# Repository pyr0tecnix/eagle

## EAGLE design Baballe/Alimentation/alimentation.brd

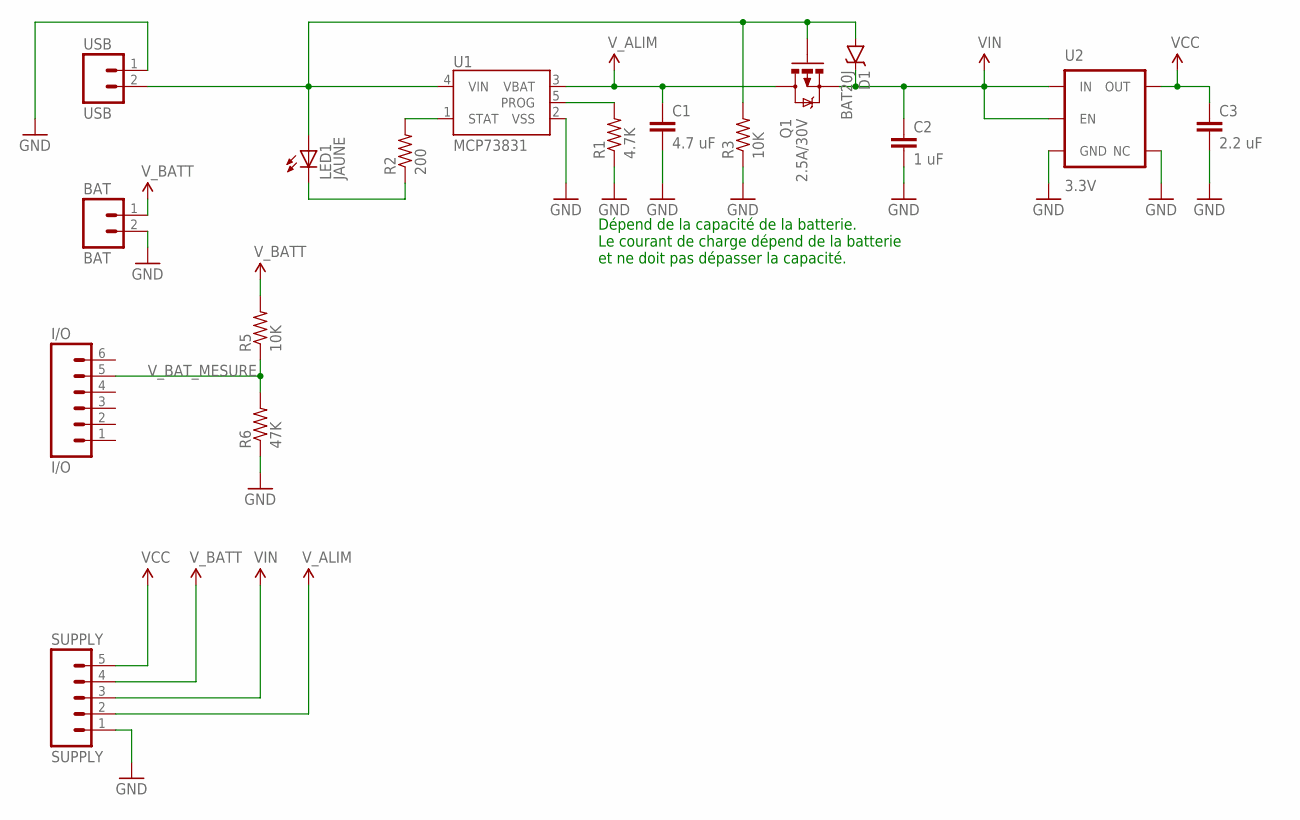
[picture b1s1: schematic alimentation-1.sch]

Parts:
BAT: BAT; 1X02_NO_SILK
C1: 4.7 uF; 0805
C2: 1 uF; 0805
C3: 2.2 uF; 0805
D1: BAT20J; SOD-323
I/O: I/O; 1X06_NO_SILK
LED1: JAUNE; LED_1206
Q1: 2.5A/30V; SOT23-3
R1: 4.7K; 0805
R2: 200; 0805
R3, R5: 10K; 0805
R6: 47K; 0805
SUPPLY: SUPPLY; 1X05_NO_SILK
U1: MCP73831; SOT23-5
U2: 3.3V; SOT23-5
USB: USB; 1X02_NO_SILK

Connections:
GND: BAT.2, C1.2, C2.2, C3.2, R1.1, R3.1, R6.1, SUPPLY.1, U1.2 (VSS), U2.2 (GND), U2.4 (NC), USB.1
unnamed: LED1.C, R2.1
unnamed: R1.2, U1.5 (PROG)
unnamed: R2.2, U1.1 (STAT)
VCC: C3.1, SUPPLY.5, U2.5 (OUT)
VCC_2: C1.1, Q1.3 (D), SUPPLY.2, U1.3 (VBAT)
VIN: C2.1, D1.C, Q1.2 (S), SUPPLY.3, U2.1 (IN), U2.3 (EN)
VUSB: D1.A, LED1.A, Q1.1 (G), R3.2, U1.4 (VIN), USB.2
V_BATT: BAT.1, R5.2, SUPPLY.4
V_BAT_MESURE: I/O.5, R5.1, R6.2

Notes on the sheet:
Dépend de la capacité de la batterie. Le courant de charge dépend de la batterie et ne doit pas dépasser la capacité.

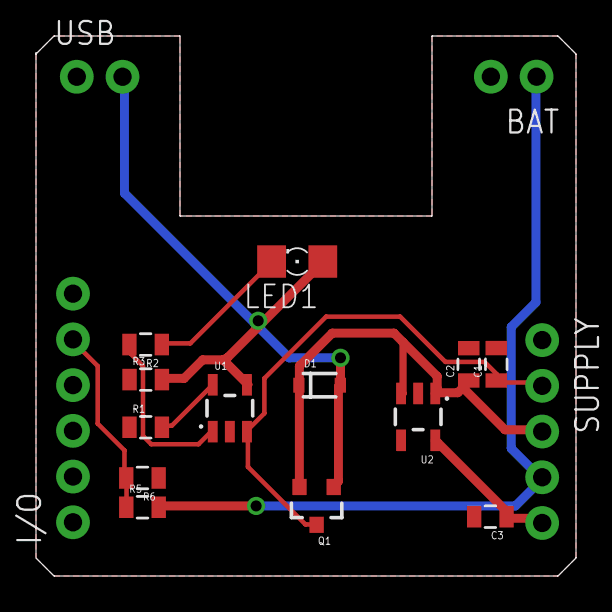
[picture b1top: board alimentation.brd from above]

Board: 2 copper layers, 30.0 x 30.0 mm, 17 parts (0 on the bottom side), 10 nets.

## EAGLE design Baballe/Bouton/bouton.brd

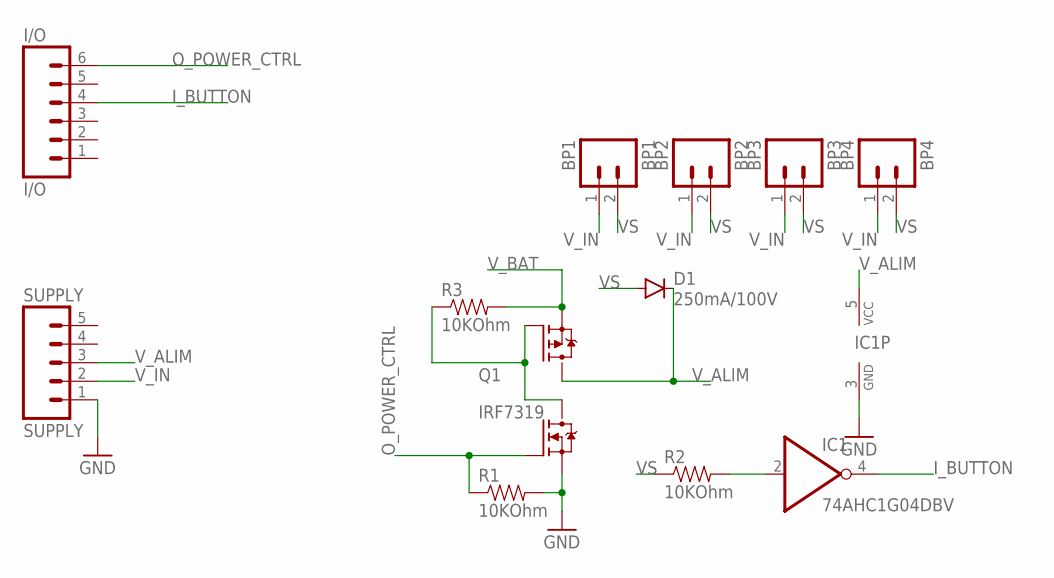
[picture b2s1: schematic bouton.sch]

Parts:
BP1: BP1; 1X02_NO_SILK
BP2: BP2; 1X02_NO_SILK
BP3: BP3; 1X02_NO_SILK
BP4: BP4; 1X02_NO_SILK
D1: 250mA/100V; SOD-323
I/O: I/O; 1X06_NO_SILK
IC1: 74AHC1G04DBV; SOT23-5
Q1: IRF7319; SO08-IRF
R1, R2, R3: 10KOhm; 0805
SUPPLY: SUPPLY; 1X05_NO_SILK

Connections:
GND: IC1.3 (GND), Q1.1 (N-S), R1.2, SUPPLY.1
I_BUTTON: I/O.4, IC1.4 (O)
unnamed: Q1.4 (P-G), Q1.7 (N-D), Q1.8 (N-D), R3.1
unnamed: IC1.2 (I), R2.2
O_POWER_CTRL: I/O.6, Q1.2 (N-G), R1.1
VS: BP1.2, BP2.2, BP3.2, BP4.2, D1.A, R2.1
V_ALIM: D1.C, IC1.5 (VCC), Q1.5 (P-D), Q1.6 (P-D), SUPPLY.3
V_BAT: Q1.3 (P-S), R3.2
V_IN: BP1.1, BP2.1, BP3.1, BP4.1, SUPPLY.2

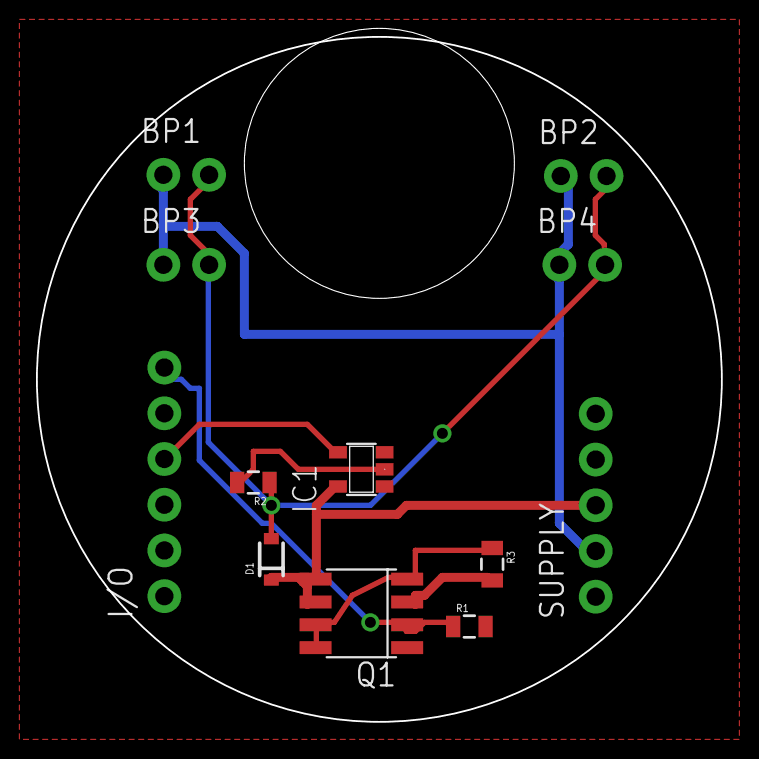
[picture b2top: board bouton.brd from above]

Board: 2 copper layers, 38.1 x 38.1 mm, 12 parts (0 on the bottom side), 9 nets.

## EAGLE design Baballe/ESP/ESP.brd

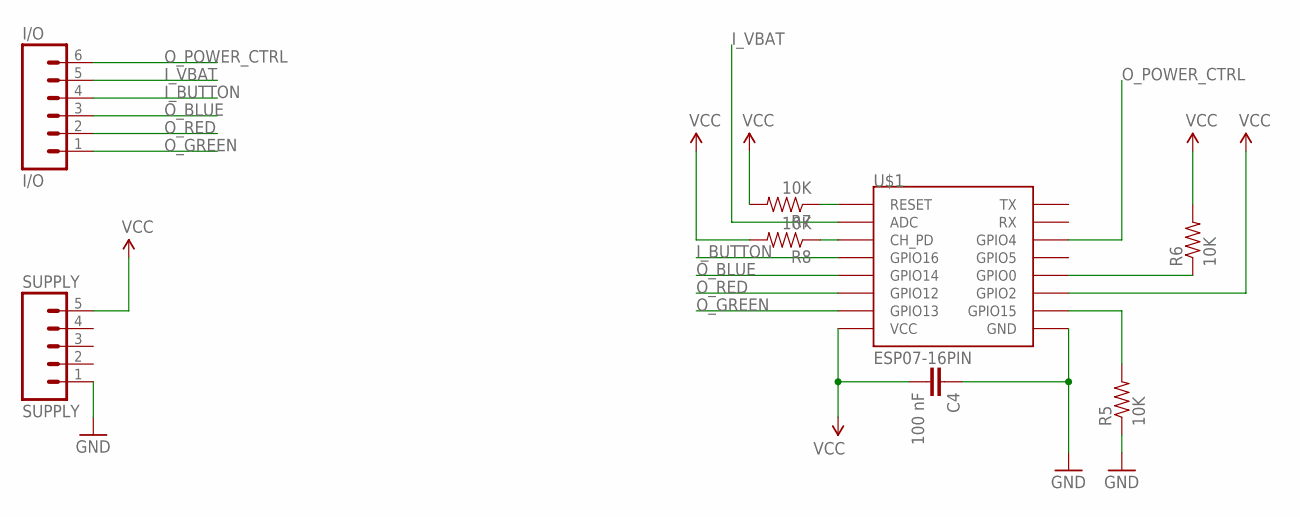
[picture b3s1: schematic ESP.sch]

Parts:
C4: 100 nF; 0805
I/O: I/O; 1X06_NO_SILK
R5, R6, R7, R8: 10K; 0805
SUPPLY: SUPPLY; 1X05_NO_SILK
U$1: ESP07-16PIN

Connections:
GND: C4.1, R5.1, SUPPLY.1, U$1.GND
I_BUTTON: I/O.4, U$1.GPIO16
I_VBAT: I/O.5, U$1.ADC
unnamed: R5.2, U$1.GPIO15
unnamed: R6.1, U$1.GPIO0
unnamed: R7.1, U$1.REST (RESET)
unnamed: R8.1, U$1.CH_PD
O_BLUE: I/O.3, U$1.GPIO14
O_GREEN: I/O.1, U$1.GPIO13
O_POWER_CTRL: I/O.6, U$1.GPIO4
O_RED: I/O.2, U$1.GPIO12
VCC: C4.2, R6.2, R7.2, R8.2, SUPPLY.5, U$1.GPIO2, U$1.VCC

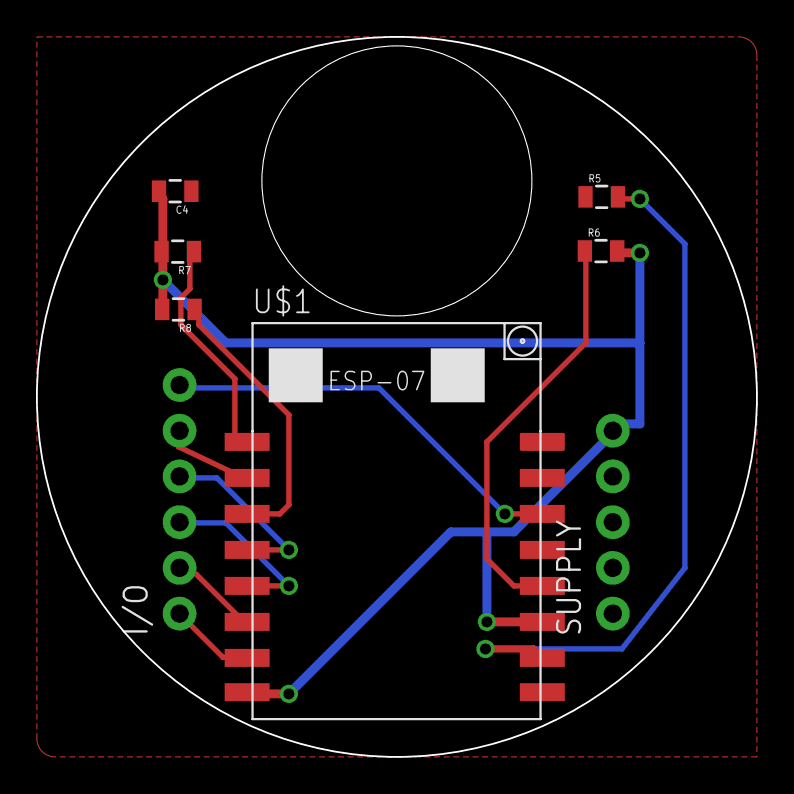
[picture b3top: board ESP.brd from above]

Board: 2 copper layers, 40.0 x 40.0 mm, 8 parts (0 on the bottom side), 12 nets.

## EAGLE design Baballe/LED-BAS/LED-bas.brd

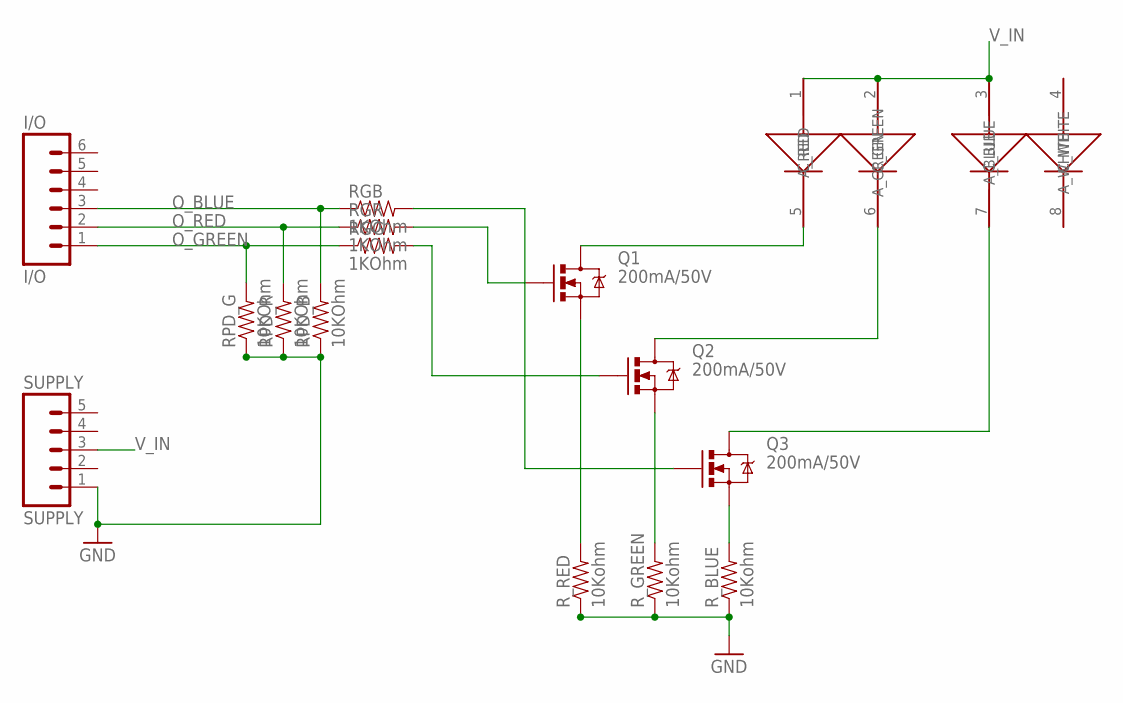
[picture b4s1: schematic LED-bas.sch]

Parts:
I/O: I/O; 1X06_NO_SILK
Q1, Q2, Q3: 200mA/50V; SOT23-3
RGB: 1KOhm; 0805
RGG: 1KOhm; 0805
RGR: 1KOhm; 0805
RPD_B: 10KOhm; 0805
RPD_G: 10KOhm; 0805
RPD_R: 10KOhm; 0805
R_BLUE: 10Kohm; 0805
R_GREEN: 10Kohm; 0805
R_RED: 10Kohm; 0805
SUPPLY: SUPPLY; 1X05_NO_SILK
U$1: CREE_MCE4CTRGBW; CLN6A

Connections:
GND: RPD_B.1, RPD_G.1, RPD_R.1, R_BLUE.1, R_GREEN.1, R_RED.1, SUPPLY.1
unnamed: Q3.2 (S), R_BLUE.2
unnamed: Q2.2 (S), R_GREEN.2
unnamed: Q1.2 (S), R_RED.2
unnamed: Q2.1 (G), RGG.2
unnamed: Q1.1 (G), RGR.2
unnamed: Q3.1 (G), RGB.2
unnamed: Q1.3 (D), U$1.5 (C_RED)
unnamed: Q2.3 (D), U$1.6 (C_GREEN)
unnamed: Q3.3 (D), U$1.7 (C_BLUE)
O_BLUE: I/O.3, RGB.1, RPD_B.2
O_GREEN: I/O.1, RGG.1, RPD_G.2
O_RED: I/O.2, RGR.1, RPD_R.2
V_IN: SUPPLY.3, U$1.1 (A_RED), U$1.2 (A_GREEN), U$1.3 (A_BLUE)

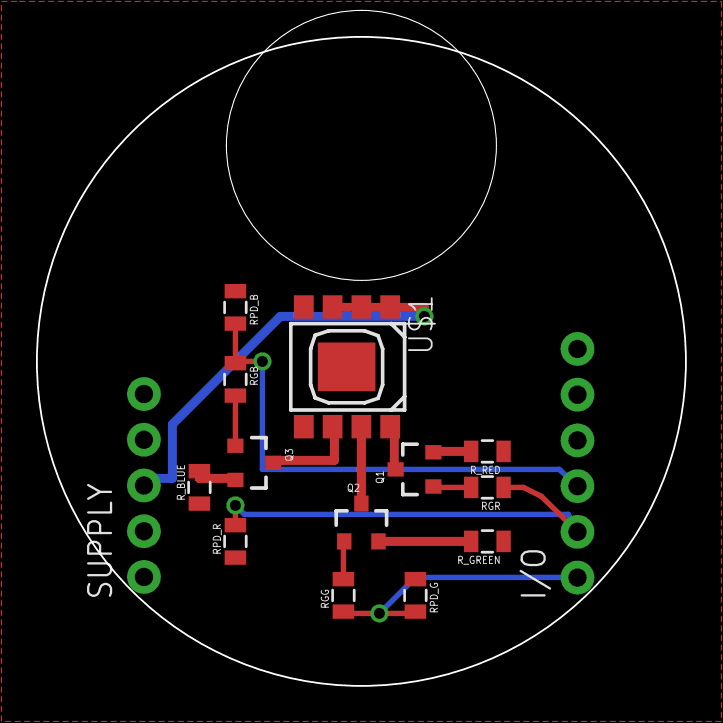
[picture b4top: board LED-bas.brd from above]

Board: 2 copper layers, 36.1 x 36.1 mm, 15 parts (0 on the bottom side), 14 nets.

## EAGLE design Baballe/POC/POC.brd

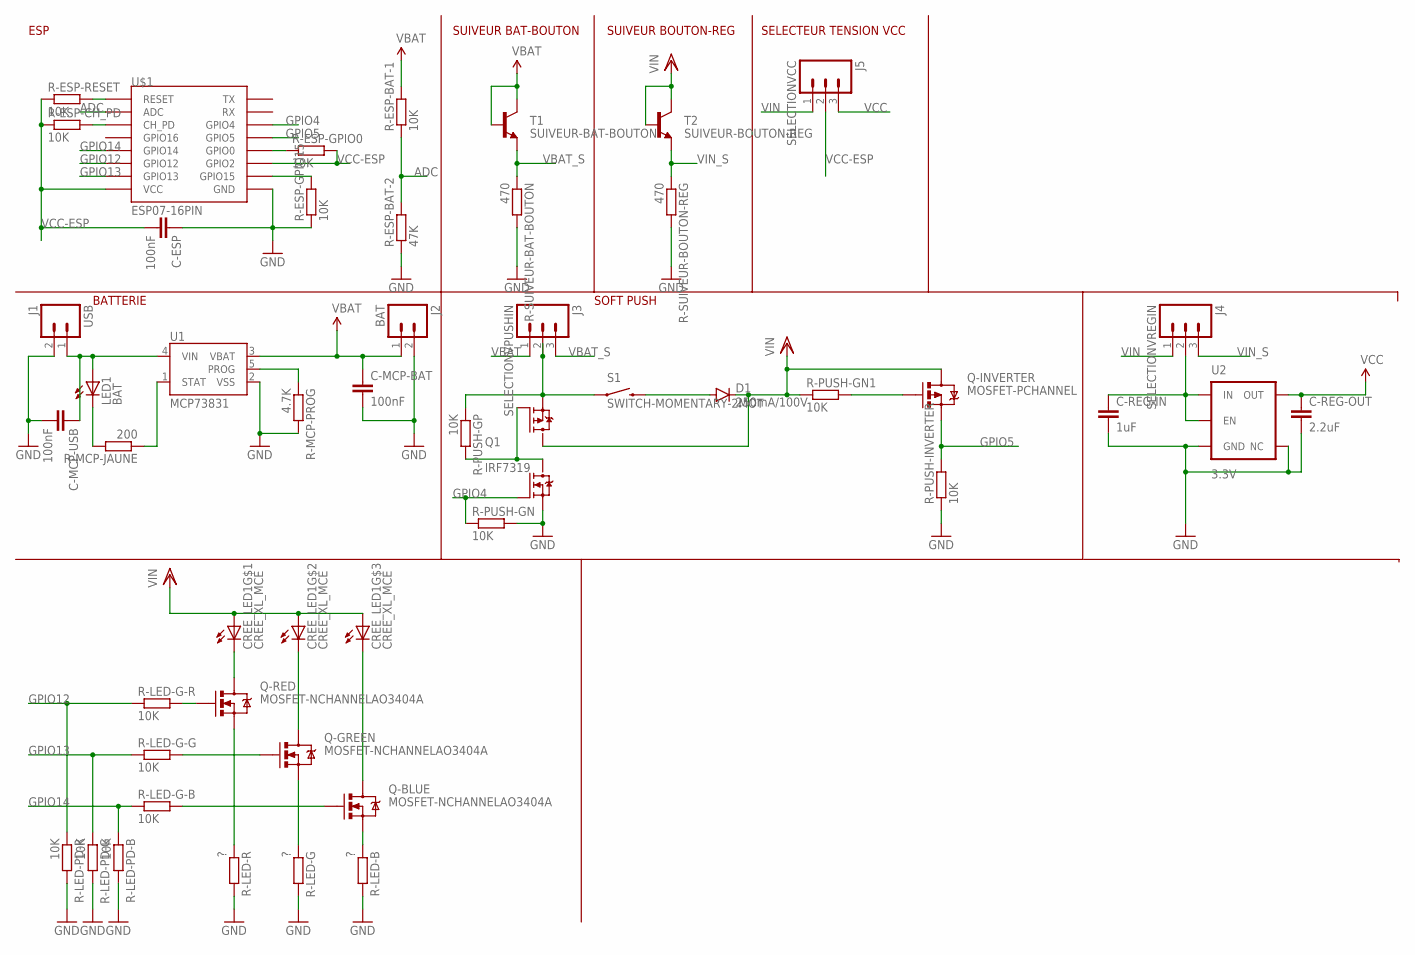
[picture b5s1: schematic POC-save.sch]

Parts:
C-ESP: 100nF; C0805
C-MCP-BAT: 100nF; C0805
C-MCP-USB: 100nF; C0805
C-REG-IN: 1uF; C0805
C-REG-OUT: 2.2uF; C0805
CREE_LED1: CREE_XL_MCE
D1: 250mA/100V; SOD-323
J1: USB; 1X02
J2: BAT; 1X02
J3: SELECTIONVPUSHIN; 1X03
J4: SELECTIONVREGIN; 1X03
J5: SELECTIONVCC; 1X03
LED1: BAT; CHIPLED_0805
Q1: IRF7319; SO08-IRF
Q-BLUE: MOSFET-NCHANNELAO3404A; SOT23-3
Q-GREEN: MOSFET-NCHANNELAO3404A; SOT23-3
Q-INVERTER: MOSFET-PCHANNEL; SOT23-3
Q-RED: MOSFET-NCHANNELAO3404A; SOT23-3
R-ESP-BAT-1: 10K; M0805
R-ESP-BAT-2: 47K; M0805
R-ESP-CH_PD: 10K; M0805
R-ESP-GPIO0, R-ESP-GPIO15: 10K; M0805
R-ESP-RESET: 10K; M0805
R-LED-B: ?; M0805
R-LED-G: ?; M0805
R-LED-G-B: 10K; M0805
R-LED-G-G: 10K; M0805
R-LED-G-R: 10K; M0805
R-LED-PD-B: 10K; M0805
R-LED-PD-G: 10K; M0805
R-LED-PD-R: 10K; M0805
R-LED-R: ?; M0805
R-MCP-JAUNE: 200; M0805
R-MCP-PROG: 4.7K; M0805
R-PUSH-GN, R-PUSH-GN1: 10K; M0805
R-PUSH-GP: 10K; M0805
R-PUSH-INVERTER: 10K; M0805
R-SUIVEUR-BAT-BOUTON: 470; M0805
R-SUIVEUR-BOUTON-REG: 470; M0805
S1: SWITCH-MOMENTARY-2MOT; TACTILE-PTH
T1: SUIVEUR-BAT-BOUTON; SOT23-3
T2: SUIVEUR-BOUTON-REG; SOT23-3
U1: MCP73831; SOT23-5
U2: 3.3V; SOT23-5
U$1: ESP07-16PIN

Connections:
ADC: R-ESP-BAT-1.1, R-ESP-BAT-2.2, U$1.ADC
GND: C-ESP.1, C-MCP-BAT.2, C-MCP-USB.2, C-REG-IN.2, C-REG-OUT.2, J1.2, J2.2, Q1.1 (N-S), R-ESP-BAT-2.1, R-ESP-GPIO15.1, R-LED-B.2, R-LED-G.2, R-LED-PD-B.2, R-LED-PD-G.2, R-LED-PD-R.2, R-LED-R.2, R-MCP-PROG.2, R-PUSH-GN.2, R-PUSH-INVERTER.1, R-SUIVEUR-BAT-BOUTON.2, R-SUIVEUR-BOUTON-REG.2, U1.2 (VSS), U2.2 (GND), U2.4 (NC), U$1.GND
GPIO4: Q1.2 (N-G), R-PUSH-GN.1, U$1.GPIO4
GPIO5: Q-INVERTER.2 (S), R-PUSH-INVERTER.2, U$1.GPIO5
GPIO12: R-LED-G-R.1, R-LED-PD-R.1, U$1.GPIO12
GPIO13: R-LED-G-G.1, R-LED-PD-G.1, U$1.GPIO13
GPIO14: R-LED-G-B.1, R-LED-PD-B.1, U$1.GPIO14
unnamed: R-ESP-GPIO15.2, U$1.GPIO15
unnamed: R-ESP-GPIO0.1, U$1.GPIO0
unnamed: R-ESP-CH_PD.2, U$1.CH_PD
unnamed: R-ESP-RESET.2, U$1.REST (RESET)
unnamed: R-MCP-PROG.1, U1.5 (PROG)
unnamed: R-MCP-JAUNE.1, U1.1 (STAT)
unnamed: LED1.C, R-MCP-JAUNE.2
unnamed: Q1.4 (P-G), Q1.7 (N-D), Q1.8 (N-D), R-PUSH-GP.2
unnamed: D1.A, S1.4 (2)
unnamed: Q-INVERTER.1 (G), R-PUSH-GN1.2
unnamed: C-REG-IN.1, J4.2, U2.1 (IN), U2.3 (EN)
unnamed: CREE_LED1.8 (C), Q-RED.3 (D)
unnamed: CREE_LED1.7 (C), Q-GREEN.3 (D)
unnamed: CREE_LED1.6 (C), Q-BLUE.3 (D)
unnamed: Q-BLUE.2 (S), R-LED-B.1
unnamed: Q-GREEN.2 (S), R-LED-G.1
unnamed: Q-RED.2 (S), R-LED-R.1
unnamed: Q-RED.1 (G), R-LED-G-R.2
unnamed: Q-GREEN.1 (G), R-LED-G-G.2
unnamed: Q-BLUE.1 (G), R-LED-G-B.2
VBAT: C-MCP-BAT.1, J2.1, J3.1, R-ESP-BAT-1.2, T1.1 (B), T1.3 (C), U1.3 (VBAT)
VBAT_S: J3.3, R-SUIVEUR-BAT-BOUTON.1, T1.2 (E)
VCC: C-REG-OUT.1, J5.3, U2.5 (OUT)
VCC-ESP: C-ESP.2, J5.2, R-ESP-CH_PD.1, R-ESP-GPIO0.2, R-ESP-RESET.1, U$1.GPIO2, U$1.VCC
VIN: CREE_LED1.1 (A), CREE_LED1.2 (A), CREE_LED1.3 (A), D1.C, J4.1, J5.1, Q1.5 (P-D), Q1.6 (P-D), Q-INVERTER.3 (D), R-PUSH-GN1.1, T2.1 (B), T2.3 (C)
VIN_S: J4.3, R-SUIVEUR-BOUTON-REG.1, T2.2 (E)
VPUSH_IN: J3.2, Q1.3 (P-S), R-PUSH-GP.1, S1.1
VUSB: C-MCP-USB.1, J1.1, LED1.A, U1.4 (VIN)

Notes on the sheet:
ESP
BATTERIE
SUIVEUR BAT-BOUTON
SOFT PUSH
SUIVEUR BOUTON-REG
SELECTEUR TENSION VCC

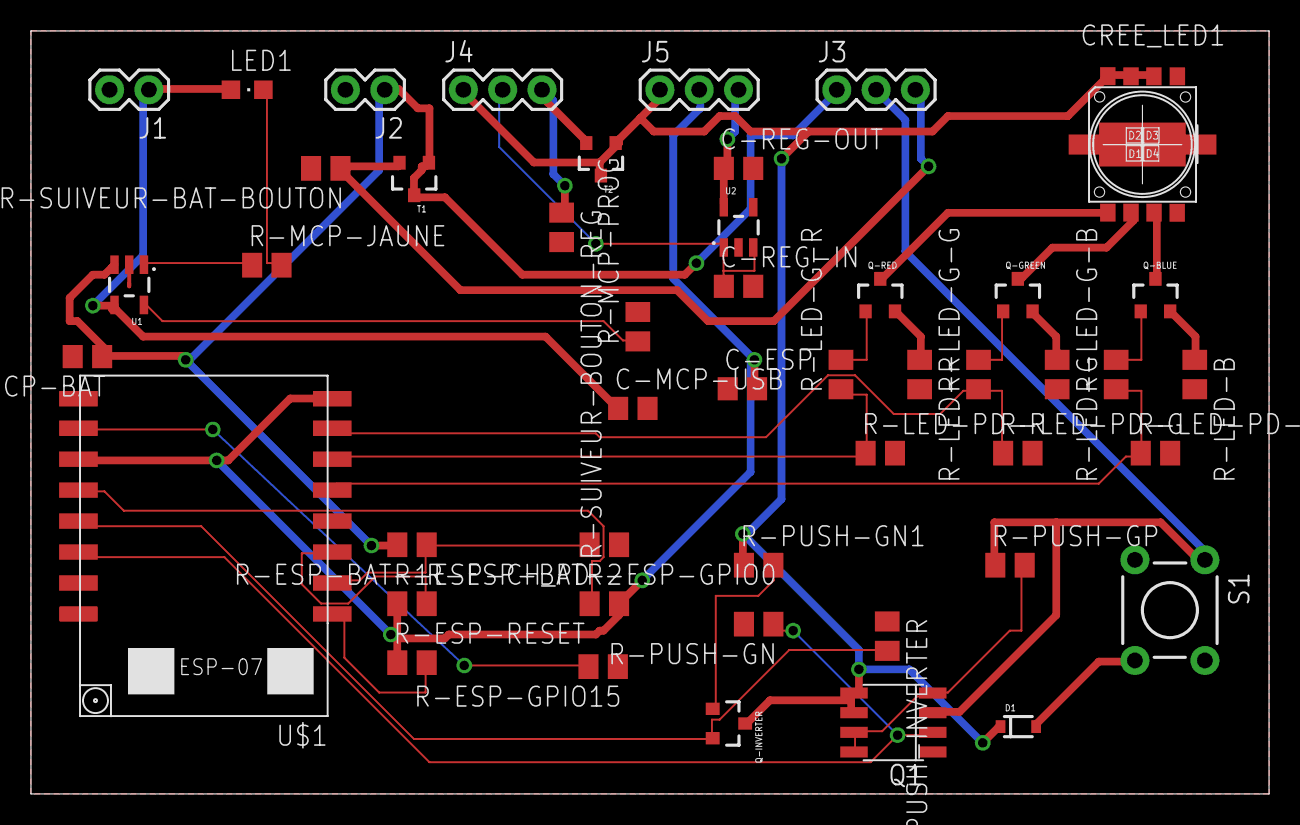
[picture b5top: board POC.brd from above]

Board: 2 copper layers, 80.0 x 49.3 mm, 47 parts (0 on the bottom side), 35 nets.

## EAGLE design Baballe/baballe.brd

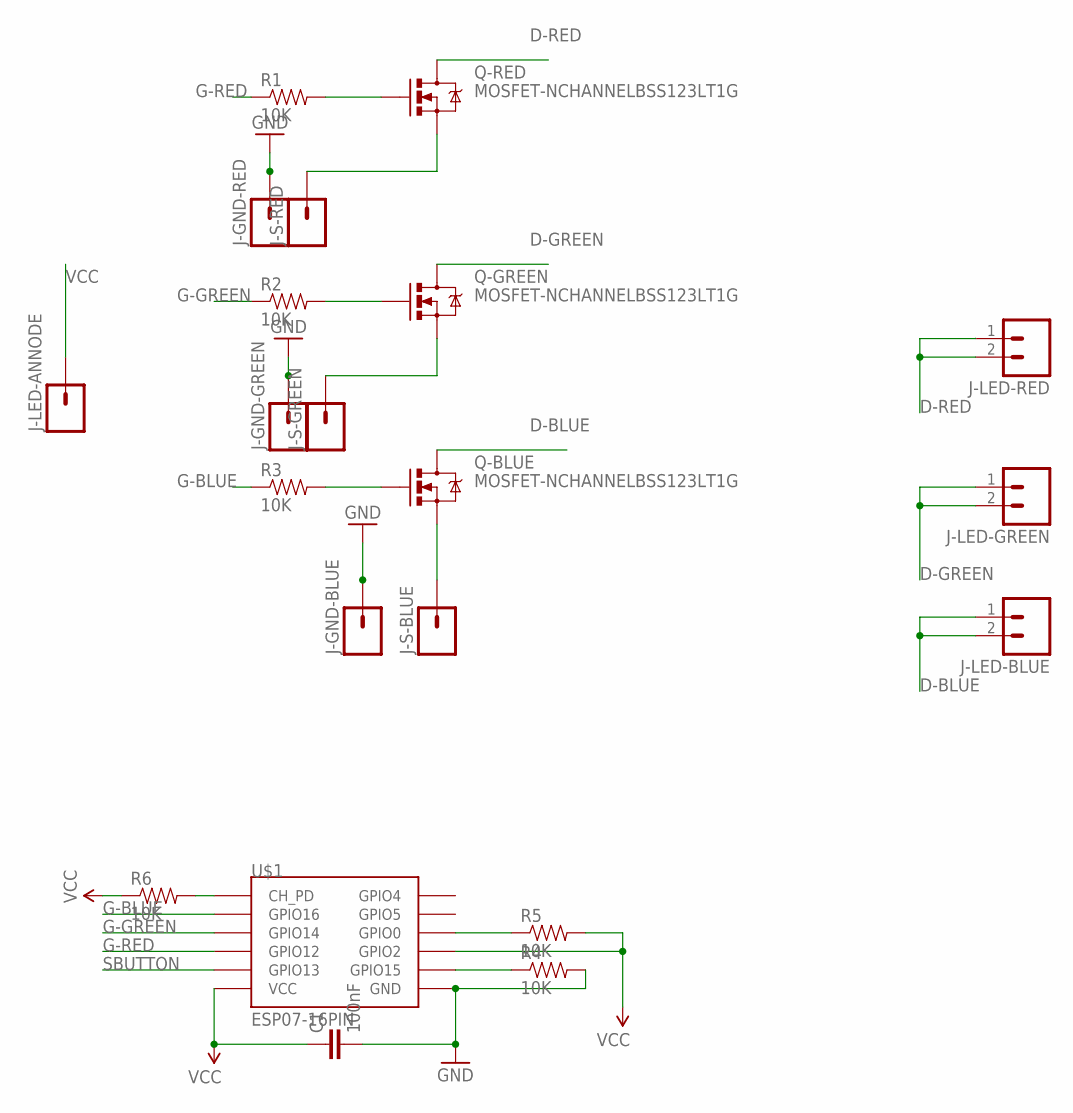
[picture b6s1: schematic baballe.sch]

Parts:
C1: 100nF; 0805
J-GND-BLUE: M01PTH; 1X01
J-GND-GREEN: M01PTH; 1X01
J-GND-RED: M01PTH; 1X01
J-LED-ANNODE: M01; 1X01-SMALL
J-LED-BLUE: M02; 1X02_SQUARE
J-LED-GREEN: M02; 1X02_SQUARE
J-LED-RED: M02; 1X02_SQUARE
J-S-BLUE: M01PTH; 1X01
J-S-GREEN: M01PTH; 1X01
J-S-RED: M01PTH; 1X01
Q-BLUE: MOSFET-NCHANNELBSS123LT1G; SOT23-3
Q-GREEN: MOSFET-NCHANNELBSS123LT1G; SOT23-3
Q-RED: MOSFET-NCHANNELBSS123LT1G; SOT23-3
R1, R2, R3, R4, R5, R6: 10K; 0805
U$1: ESP07-16PIN

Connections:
D-BLUE: J-LED-BLUE.1, J-LED-BLUE.2, Q-BLUE.3 (D)
D-GREEN: J-LED-GREEN.1, J-LED-GREEN.2, Q-GREEN.3 (D)
D-RED: J-LED-RED.1, J-LED-RED.2, Q-RED.3 (D)
G-BLUE: R3.1, U$1.GPIO16
G-GREEN: R2.1, U$1.GPIO14
G-RED: R1.1, U$1.GPIO12
GND: C1.2, J-GND-BLUE.1, J-GND-GREEN.1, J-GND-RED.1, R4.2, U$1.GND
unnamed: Q-RED.1 (G), R1.2
unnamed: Q-GREEN.1 (G), R2.2
unnamed: Q-BLUE.1 (G), R3.2
unnamed: R6.2, U$1.CH_PD
unnamed: R5.1, U$1.GPIO0
unnamed: R4.1, U$1.GPIO15
unnamed: J-S-RED.1, Q-RED.2 (S)
unnamed: J-S-GREEN.1, Q-GREEN.2 (S)
unnamed: J-S-BLUE.1, Q-BLUE.2 (S)
SBUTTON: U$1.GPIO13
VCC: C1.1, J-LED-ANNODE.1, R5.2, R6.1, U$1.GPIO2, U$1.VCC

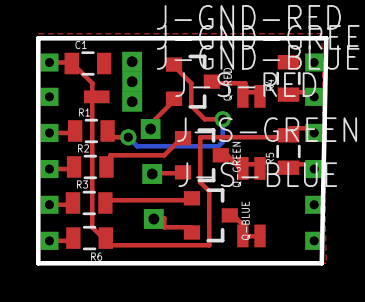
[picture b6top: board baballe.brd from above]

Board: 2 copper layers, 16.0 x 12.5 mm, 21 parts (1 on the bottom side), 17 nets.

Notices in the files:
parts and their libraries:
SparkFun-Aesthetics: Licensing: Creative Commons ShareAlike 4.0 International - https://creativecommons.org/licenses/by-sa/4.0
